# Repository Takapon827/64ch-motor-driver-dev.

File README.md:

# 64ch Motor Driver Board — FIELD MOTOR BOARD v1.0

I2C接続で最大64チャンネルのモーターを独立PWM制御できる基板です。

## 概要

| 項目 | 内容 |
|------|------|
| チャンネル数 | 64ch（MOT00〜MOT63） |
| 制御方式 | I2C（PWMコントローラ経由） |
| 電源 | DC 5V / 12A（センタープラス） |
| 基板層数 | 2層（1.6mm厚） |
| ツール | KiCad 9.0 |

## 回路構成

```
Host (Arduino等)
    │  I2C (SDA / SCL)
    ▼
PCA9685 × 4 (0x40 / 0x41 / 0x42 / 0x43)
    │  PWM × 64ch
    ▼
ULN2803A × 8  (Darlington Transistor Array, 8ch each)
    │  Open Collector × 64ch
    ▼
JST PH 2pin コネクタ × 64個 (MOT00〜MOT63)
    │
    ▼
モーター / ソレノイド 等
```

## 主要部品

| 部品 | 型番 | 数量 | 役割 |
|------|------|------|------|
| PWMコントローラ | PCA9685 | 4 | I2C→PWM変換、16ch/IC |
| トランジスタアレイ | ULN2803A | 8 | モータードライブ、8ch/IC |
| モーター出力コネクタ | JST PH B2B-PH-K（2ピン） | 64 | MOT00〜MOT63 |
| ポリヒューズ | PPTC 10A | 1 | 電源保護 |
| プルアップ抵抗 | 4.7kΩ | 2 | SDA / SCL |
| デカップリングコンデンサ | 100nF (0402/0805) | 12 | 各IC電源デカップリング |
| 電解コンデンサ | 100μF/10V | 2 | バルクキャパシタ |
| 電解コンデンサ | 1000μF/10V | 2 | バルクキャパシタ |
| 取り付け穴 | M3 | 4 | ボード固定用 |

## I2Cアドレス

| IC | アドレス | 制御チャンネル |
|----|----------|----------------|
| PCA9685 #1 | 0x40 | MOT00〜MOT15 |
| PCA9685 #2 | 0x41 | MOT16〜MOT31 |
| PCA9685 #3 | 0x42 | MOT32〜MOT47 |
| PCA9685 #4 | 0x43 | MOT48〜MOT63 |

基板上にはアドレス確認用テストパッドが実装されています。

## 接続

### 電源
- コネクタ: DC バレルジャック（センタープラス）
- 入力: **DC 5V / 12A**

### I2C（Arduinoヘッダ）
| ピン | 信号 |
|------|------|
| SDA | I2Cデータ |
| SCL | I2Cクロック |
| GND | グラウンド |
| +5V | 電源（ホストへ給電 or 受電） |

### モーター出力
- コネクタ: JST PH 2ピン（2.00mmピッチ）
- 出力: ULN2803A オープンコレクタ
- 最大連続電流: 500mA / ch（ULN2803A定格）

## 注意事項

> **[!] PWM MAX DUTY 25% → 1.2V avg**
>
> 各チャンネルのPWMデューティ比は最大25%を推奨します。  
> 5V電源時の平均電圧は約1.2Vとなります。  
> これを超えると部品の発熱・損傷の原因になります。

- ULN2803Aは誘導負荷（モーター）に対して内部保護ダイオードを持ちますが、大電流負荷には追加のフライバックダイオードを検討してください。
- 全チャンネル同時駆動時は電源容量（12A）に注意してください。

## 開発環境

- KiCad 9.0

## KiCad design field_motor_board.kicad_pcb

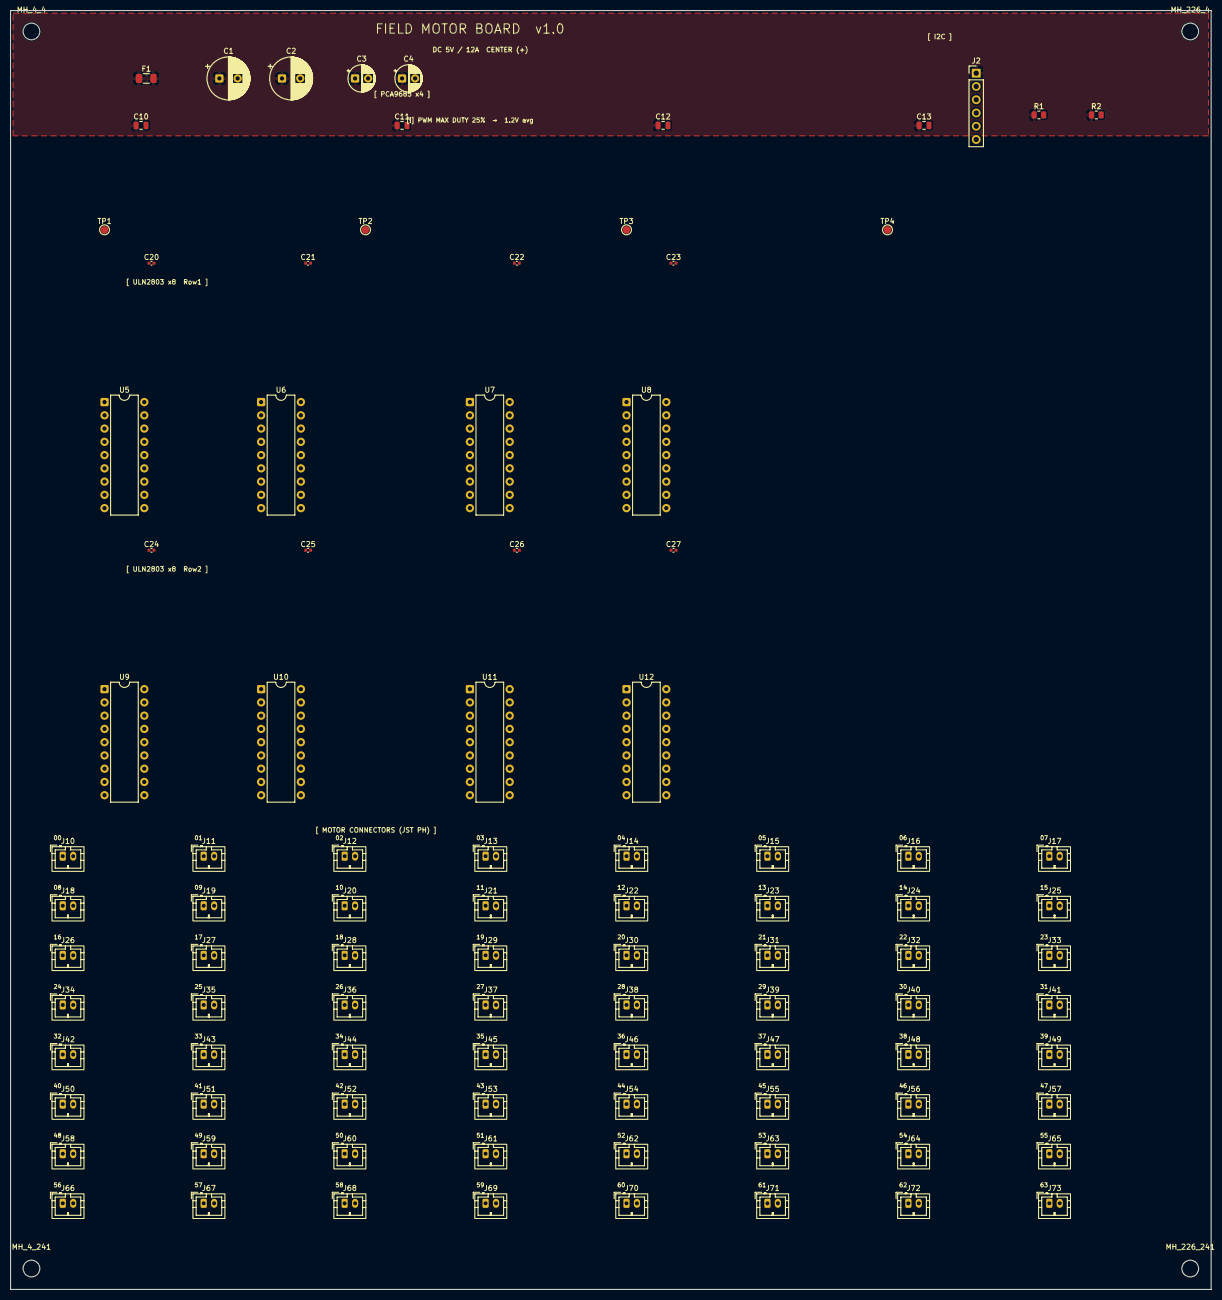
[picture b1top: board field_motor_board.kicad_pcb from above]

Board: 2 copper layers, 230.0 x 245.0 mm, 100 parts (0 on the bottom side), 68 nets, no tracks yet.

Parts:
C1, C2: 1000uF/10V; CP_Radial_D8.0mm_P3.50mm
C3, C4: 100uF/10V; CP_Radial_D5.0mm_P2.50mm
C10, C11, C12, C13: 100nF; C_0805_2012Metric
C20, C21, C22, C23, C24, C25, C26, C27: 100nF; C_0402_1005Metric
F1: PPTC 10A; Fuse_1206_3216Metric
J2: ARDUINO HEADER; PinHeader_1x06_P2.54mm_Vertical
J10: MOT00; JST_PH_B2B-PH-K_1x02_P2.00mm_Vertical
J11: MOT01; JST_PH_B2B-PH-K_1x02_P2.00mm_Vertical
J12: MOT02; JST_PH_B2B-PH-K_1x02_P2.00mm_Vertical
J13: MOT03; JST_PH_B2B-PH-K_1x02_P2.00mm_Vertical
J14: MOT04; JST_PH_B2B-PH-K_1x02_P2.00mm_Vertical
J15: MOT05; JST_PH_B2B-PH-K_1x02_P2.00mm_Vertical
J16: MOT06; JST_PH_B2B-PH-K_1x02_P2.00mm_Vertical
J17: MOT07; JST_PH_B2B-PH-K_1x02_P2.00mm_Vertical
J18: MOT08; JST_PH_B2B-PH-K_1x02_P2.00mm_Vertical
J19: MOT09; JST_PH_B2B-PH-K_1x02_P2.00mm_Vertical
J20: MOT10; JST_PH_B2B-PH-K_1x02_P2.00mm_Vertical
J21: MOT11; JST_PH_B2B-PH-K_1x02_P2.00mm_Vertical
J22: MOT12; JST_PH_B2B-PH-K_1x02_P2.00mm_Vertical
J23: MOT13; JST_PH_B2B-PH-K_1x02_P2.00mm_Vertical
J24: MOT14; JST_PH_B2B-PH-K_1x02_P2.00mm_Vertical
J25: MOT15; JST_PH_B2B-PH-K_1x02_P2.00mm_Vertical
J26: MOT16; JST_PH_B2B-PH-K_1x02_P2.00mm_Vertical
J27: MOT17; JST_PH_B2B-PH-K_1x02_P2.00mm_Vertical
J28: MOT18; JST_PH_B2B-PH-K_1x02_P2.00mm_Vertical
J29: MOT19; JST_PH_B2B-PH-K_1x02_P2.00mm_Vertical
J30: MOT20; JST_PH_B2B-PH-K_1x02_P2.00mm_Vertical
J31: MOT21; JST_PH_B2B-PH-K_1x02_P2.00mm_Vertical
J32: MOT22; JST_PH_B2B-PH-K_1x02_P2.00mm_Vertical
J33: MOT23; JST_PH_B2B-PH-K_1x02_P2.00mm_Vertical
J34: MOT24; JST_PH_B2B-PH-K_1x02_P2.00mm_Vertical
J35: MOT25; JST_PH_B2B-PH-K_1x02_P2.00mm_Vertical
J36: MOT26; JST_PH_B2B-PH-K_1x02_P2.00mm_Vertical
J37: MOT27; JST_PH_B2B-PH-K_1x02_P2.00mm_Vertical
J38: MOT28; JST_PH_B2B-PH-K_1x02_P2.00mm_Vertical
J39: MOT29; JST_PH_B2B-PH-K_1x02_P2.00mm_Vertical
J40: MOT30; JST_PH_B2B-PH-K_1x02_P2.00mm_Vertical
J41: MOT31; JST_PH_B2B-PH-K_1x02_P2.00mm_Vertical
J42: MOT32; JST_PH_B2B-PH-K_1x02_P2.00mm_Vertical
J43: MOT33; JST_PH_B2B-PH-K_1x02_P2.00mm_Vertical
J44: MOT34; JST_PH_B2B-PH-K_1x02_P2.00mm_Vertical
J45: MOT35; JST_PH_B2B-PH-K_1x02_P2.00mm_Vertical
J46: MOT36; JST_PH_B2B-PH-K_1x02_P2.00mm_Vertical
J47: MOT37; JST_PH_B2B-PH-K_1x02_P2.00mm_Vertical
J48: MOT38; JST_PH_B2B-PH-K_1x02_P2.00mm_Vertical
J49: MOT39; JST_PH_B2B-PH-K_1x02_P2.00mm_Vertical
J50: MOT40; JST_PH_B2B-PH-K_1x02_P2.00mm_Vertical
J51: MOT41; JST_PH_B2B-PH-K_1x02_P2.00mm_Vertical
J52: MOT42; JST_PH_B2B-PH-K_1x02_P2.00mm_Vertical
J53: MOT43; JST_PH_B2B-PH-K_1x02_P2.00mm_Vertical
J54: MOT44; JST_PH_B2B-PH-K_1x02_P2.00mm_Vertical
J55: MOT45; JST_PH_B2B-PH-K_1x02_P2.00mm_Vertical
J56: MOT46; JST_PH_B2B-PH-K_1x02_P2.00mm_Vertical
J57: MOT47; JST_PH_B2B-PH-K_1x02_P2.00mm_Vertical
J58: MOT48; JST_PH_B2B-PH-K_1x02_P2.00mm_Vertical
J59: MOT49; JST_PH_B2B-PH-K_1x02_P2.00mm_Vertical
J60: MOT50; JST_PH_B2B-PH-K_1x02_P2.00mm_Vertical
J61: MOT51; JST_PH_B2B-PH-K_1x02_P2.00mm_Vertical
J62: MOT52; JST_PH_B2B-PH-K_1x02_P2.00mm_Vertical
J63: MOT53; JST_PH_B2B-PH-K_1x02_P2.00mm_Vertical
J64: MOT54; JST_PH_B2B-PH-K_1x02_P2.00mm_Vertical
J65: MOT55; JST_PH_B2B-PH-K_1x02_P2.00mm_Vertical
J66: MOT56; JST_PH_B2B-PH-K_1x02_P2.00mm_Vertical
J67: MOT57; JST_PH_B2B-PH-K_1x02_P2.00mm_Vertical
J68: MOT58; JST_PH_B2B-PH-K_1x02_P2.00mm_Vertical
J69: MOT59; JST_PH_B2B-PH-K_1x02_P2.00mm_Vertical
J70: MOT60; JST_PH_B2B-PH-K_1x02_P2.00mm_Vertical
J71: MOT61; JST_PH_B2B-PH-K_1x02_P2.00mm_Vertical
J72: MOT62; JST_PH_B2B-PH-K_1x02_P2.00mm_Vertical
J73: MOT63; JST_PH_B2B-PH-K_1x02_P2.00mm_Vertical
MH_4_4, MH_4_241, MH_226_4, MH_226_241: M3; MountingHole_3.2mm_M3
R1: 4.7k (SCL pullup); R_0805_2012Metric
R2: 4.7k (SDA pullup); R_0805_2012Metric
TP1: ADDR 0x40; TestPoint_Pad_D1.5mm
TP2: ADDR 0x41; TestPoint_Pad_D1.5mm
TP3: ADDR 0x42; TestPoint_Pad_D1.5mm
TP4: ADDR 0x43; TestPoint_Pad_D1.5mm
U5, U6, U7, U8, U9, U10, U11, U12: ULN2803A; DIP-18_W7.62mm

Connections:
+5V: C1.1, C2.1, C3.1, C4.1, C10.1, C11.1, C12.1, C13.1, C20.1, C21.1, C22.1, C23.1, C24.1, C25.1, C26.1, C27.1, F1.1, F1.2, J2.1, J10.1, J11.1, J12.1, J13.1, J14.1, J15.1, J16.1, J17.1, J18.1, J19.1, J20.1, J21.1, J22.1, J23.1, J24.1, J25.1, J26.1, J27.1, J28.1, J29.1, J30.1, J31.1, J32.1, J33.1, J34.1, J35.1, J36.1, J37.1, J38.1, J39.1, J40.1, J41.1, J42.1, J43.1, J44.1, J45.1, J46.1, J47.1, J48.1, J49.1, J50.1, J51.1, J52.1, J53.1, J54.1, J55.1, J56.1, J57.1, J58.1, J59.1, J60.1, J61.1, J62.1, J63.1, J64.1, J65.1, J66.1, J67.1, J68.1, J69.1, J70.1, J71.1, J72.1, J73.1, R1.1, R2.1, U5.10, U6.10, U7.10, U8.10, U9.10, U10.10, U11.10, U12.10
GND: C1.2, C2.2, C3.2, C4.2, C10.2, C11.2, C12.2, C13.2, C20.2, C21.2, C22.2, C23.2, C24.2, C25.2, C26.2, C27.2, J2.2, U5.9, U6.9, U7.9, U8.9, U9.9, U10.9, U11.9, U12.9
MOT00: J10.2, U5.18
MOT01: J11.2, U5.17
MOT02: J12.2, U5.16
MOT03: J13.2, U5.15
MOT04: J14.2, U5.14
MOT05: J15.2, U5.13
MOT06: J16.2, U5.12
MOT07: J17.2, U5.11
MOT08: J18.2, U6.18
MOT09: J19.2, U6.17
MOT10: J20.2, U6.16
MOT11: J21.2, U6.15
MOT12: J22.2, U6.14
MOT13: J23.2, U6.13
MOT14: J24.2, U6.12
MOT15: J25.2, U6.11
MOT16: J26.2, U7.18
MOT17: J27.2, U7.17
MOT18: J28.2, U7.16
MOT19: J29.2, U7.15
MOT20: J30.2, U7.14
MOT21: J31.2, U7.13
MOT22: J32.2, U7.12
MOT23: J33.2, U7.11
MOT24: J34.2, U8.18
MOT25: J35.2, U8.17
MOT26: J36.2, U8.16
MOT27: J37.2, U8.15
MOT28: J38.2, U8.14
MOT29: J39.2, U8.13
MOT30: J40.2, U8.12
MOT31: J41.2, U8.11
MOT32: J42.2, U9.18
MOT33: J43.2, U9.17
MOT34: J44.2, U9.16
MOT35: J45.2, U9.15
MOT36: J46.2, U9.14
MOT37: J47.2, U9.13
MOT38: J48.2, U9.12
MOT39: J49.2, U9.11
MOT40: J50.2, U10.18
MOT41: J51.2, U10.17
MOT42: J52.2, U10.16
MOT43: J53.2, U10.15
MOT44: J54.2, U10.14
MOT45: J55.2, U10.13
MOT46: J56.2, U10.12
MOT47: J57.2, U10.11
MOT48: J58.2, U11.18
MOT49: J59.2, U11.17
MOT50: J60.2, U11.16
MOT51: J61.2, U11.15
MOT52: J62.2, U11.14
MOT53: J63.2, U11.13
MOT54: J64.2, U11.12
MOT55: J65.2, U11.11
MOT56: J66.2, U12.18
MOT57: J67.2, U12.17
MOT58: J68.2, U12.16
MOT59: J69.2, U12.15
MOT60: J70.2, U12.14
MOT61: J71.2, U12.13
MOT62: J72.2, U12.12
MOT63: J73.2, U12.11
SCL: J2.3, R1.2
SDA: J2.4, R2.2

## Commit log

2026-05-13 Add KiCad PCB file for 64ch motor driver board
2026-05-13 Replace with 64ch_motordriver.kicad_pro
2026-05-13 Add README for 64ch motor driver board
